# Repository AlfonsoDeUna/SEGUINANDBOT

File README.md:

# ROBOT EDUCATIVO PARA FP. 

Es el diseño de un robot muy sencillo realizado en KiCad. Es un seguidor de líneas utilizando el sensor CNY70, puertas lógias NAND.

Información sobre el sensor CNY70
---
https://hetpro-store.com/TUTORIALES/cny70-sensor-optico/

Basado en el proyecto inicial
---
http://www.geocities.ws/blastedrobotics/Revista_01

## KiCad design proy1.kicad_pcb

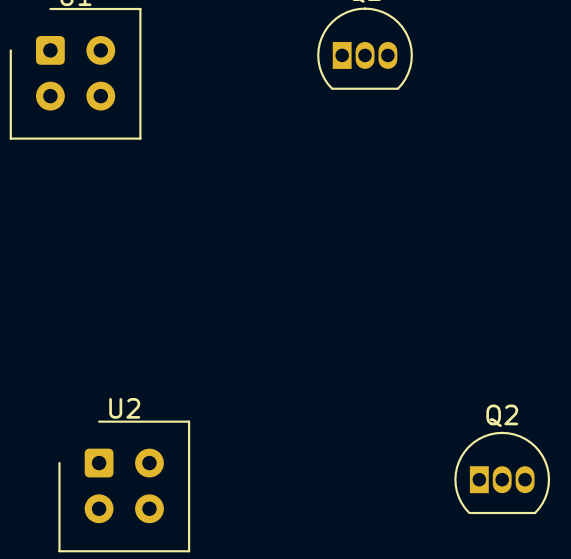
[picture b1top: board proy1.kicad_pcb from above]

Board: 2 copper layers, 4 parts (0 on the bottom side), 2 nets, no tracks yet.

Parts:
Q1, Q2: 2N3904; TO-92_Inline
U1, U2: CNY70; Vishay_CNY70

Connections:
GNDREF: Q1.1, Q2.1
VCC: U1.1, U1.3, U2.1, U2.3
